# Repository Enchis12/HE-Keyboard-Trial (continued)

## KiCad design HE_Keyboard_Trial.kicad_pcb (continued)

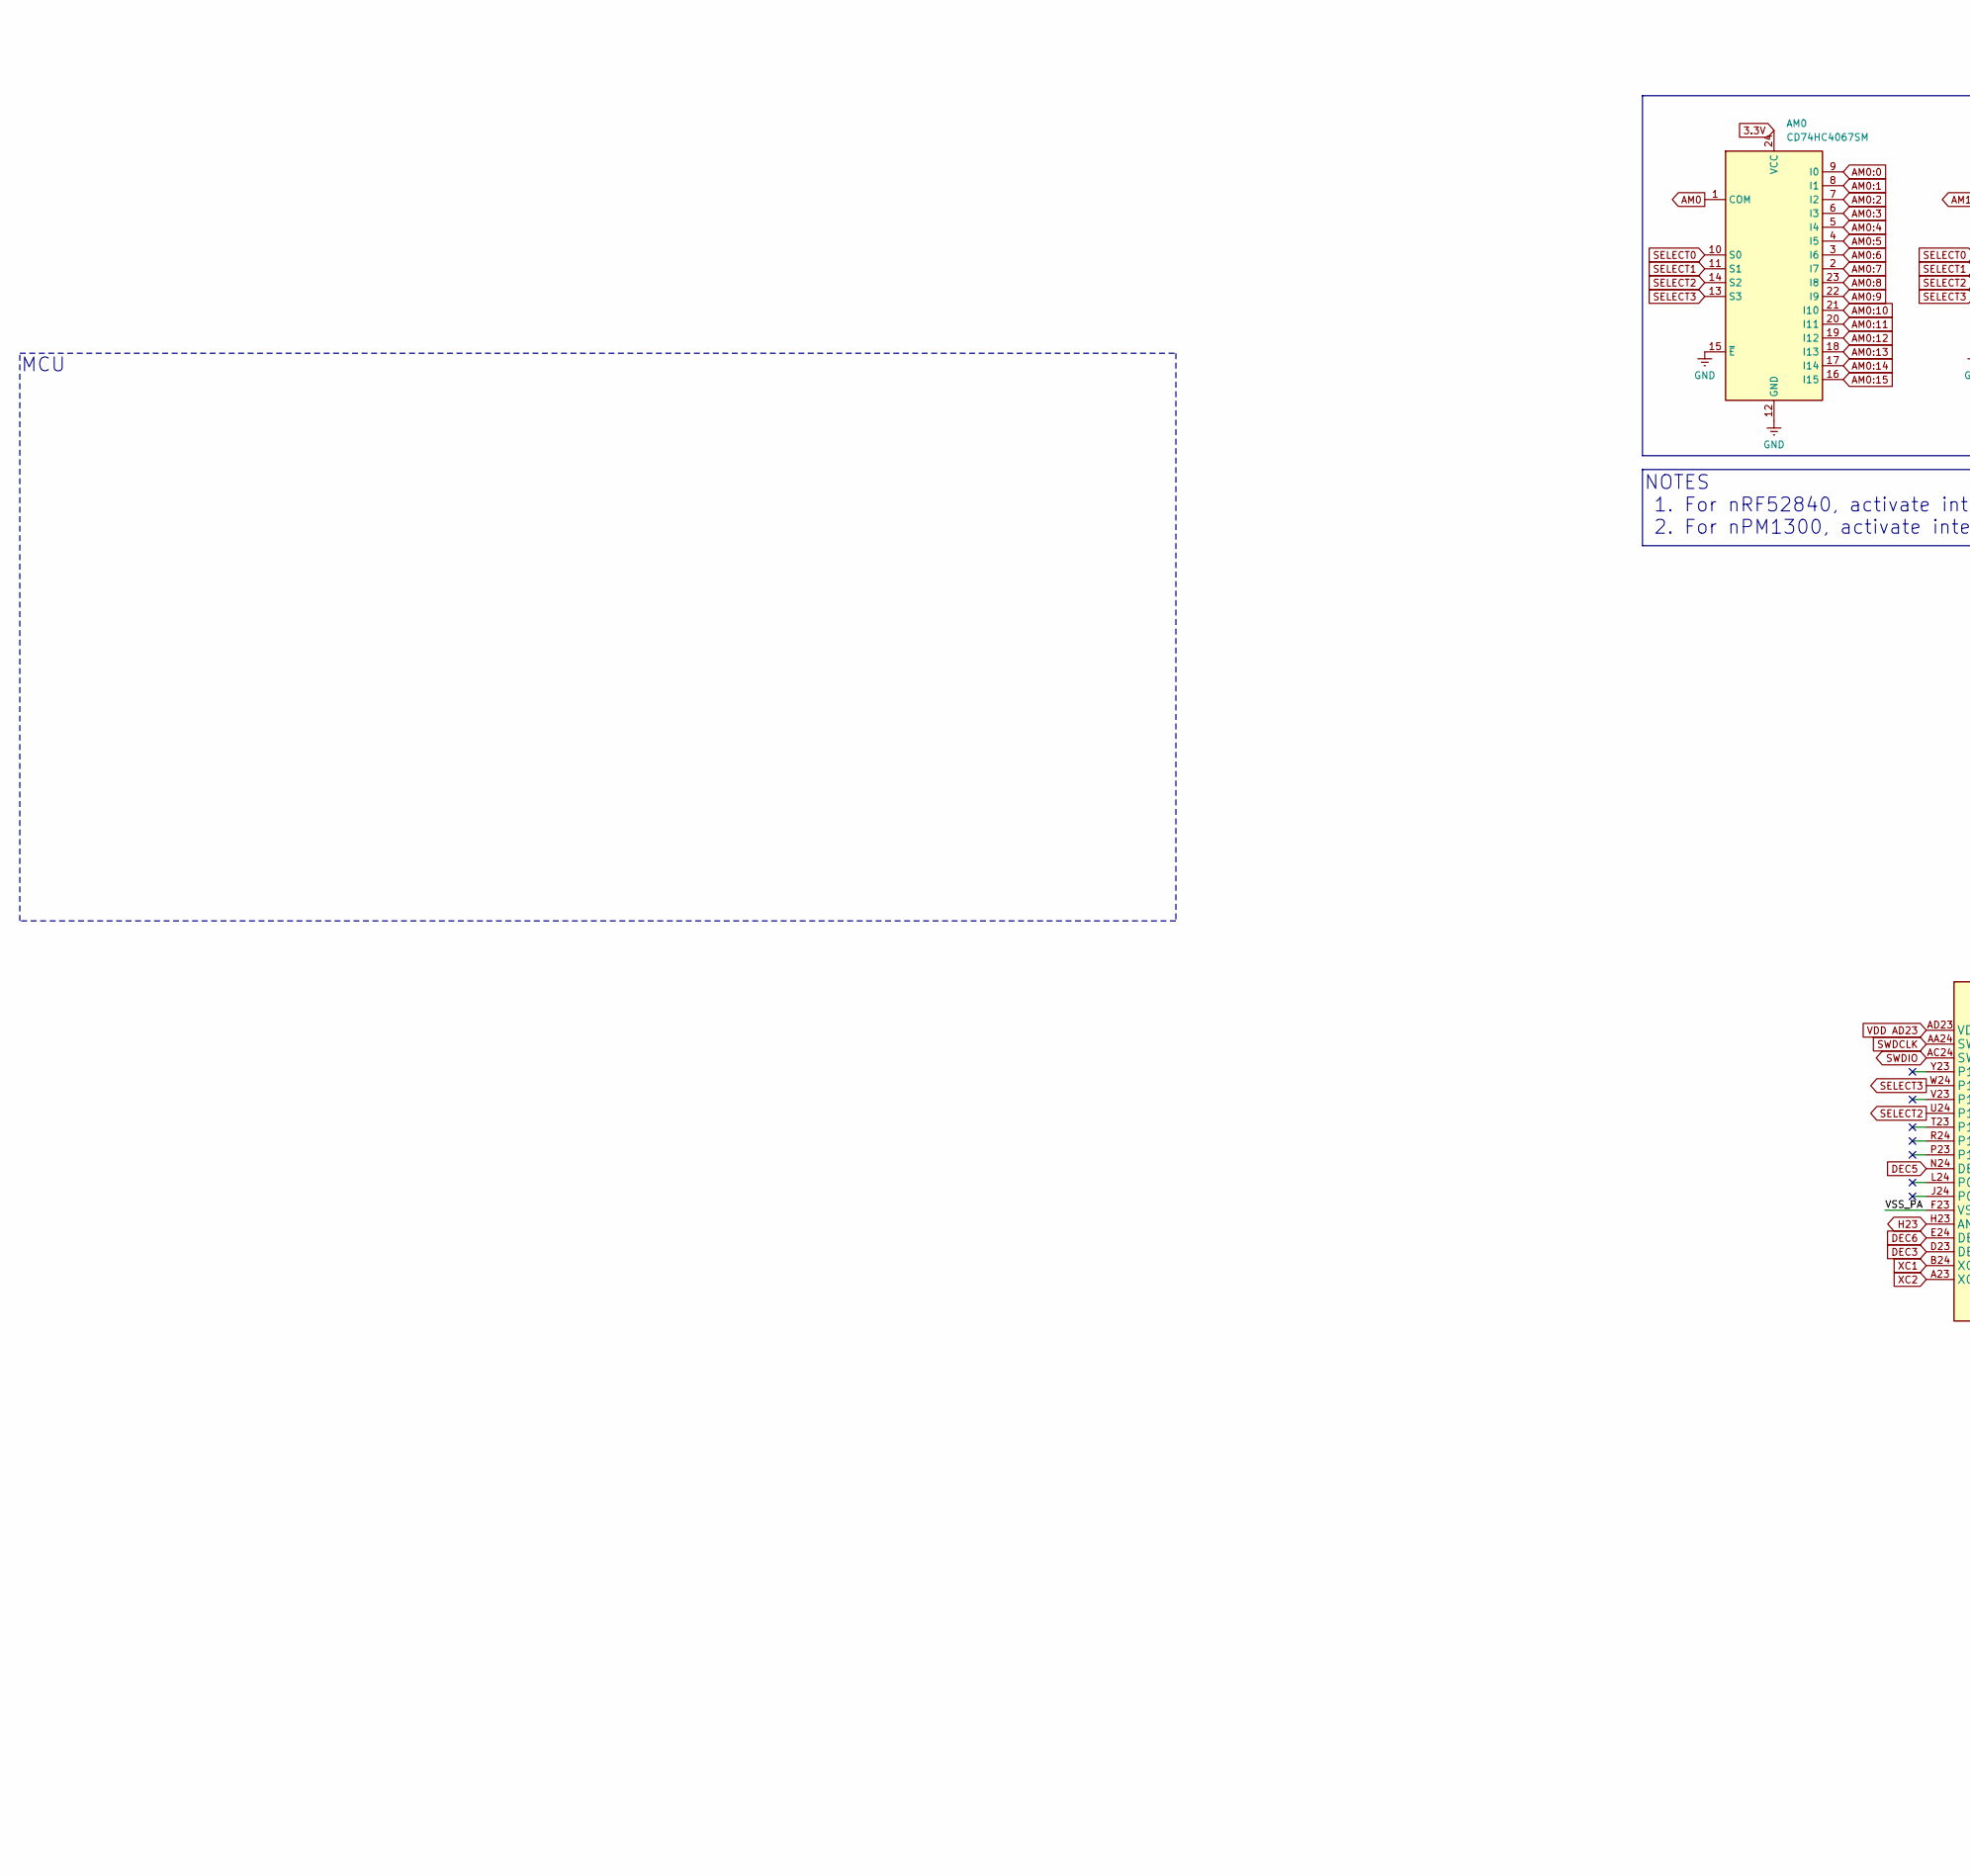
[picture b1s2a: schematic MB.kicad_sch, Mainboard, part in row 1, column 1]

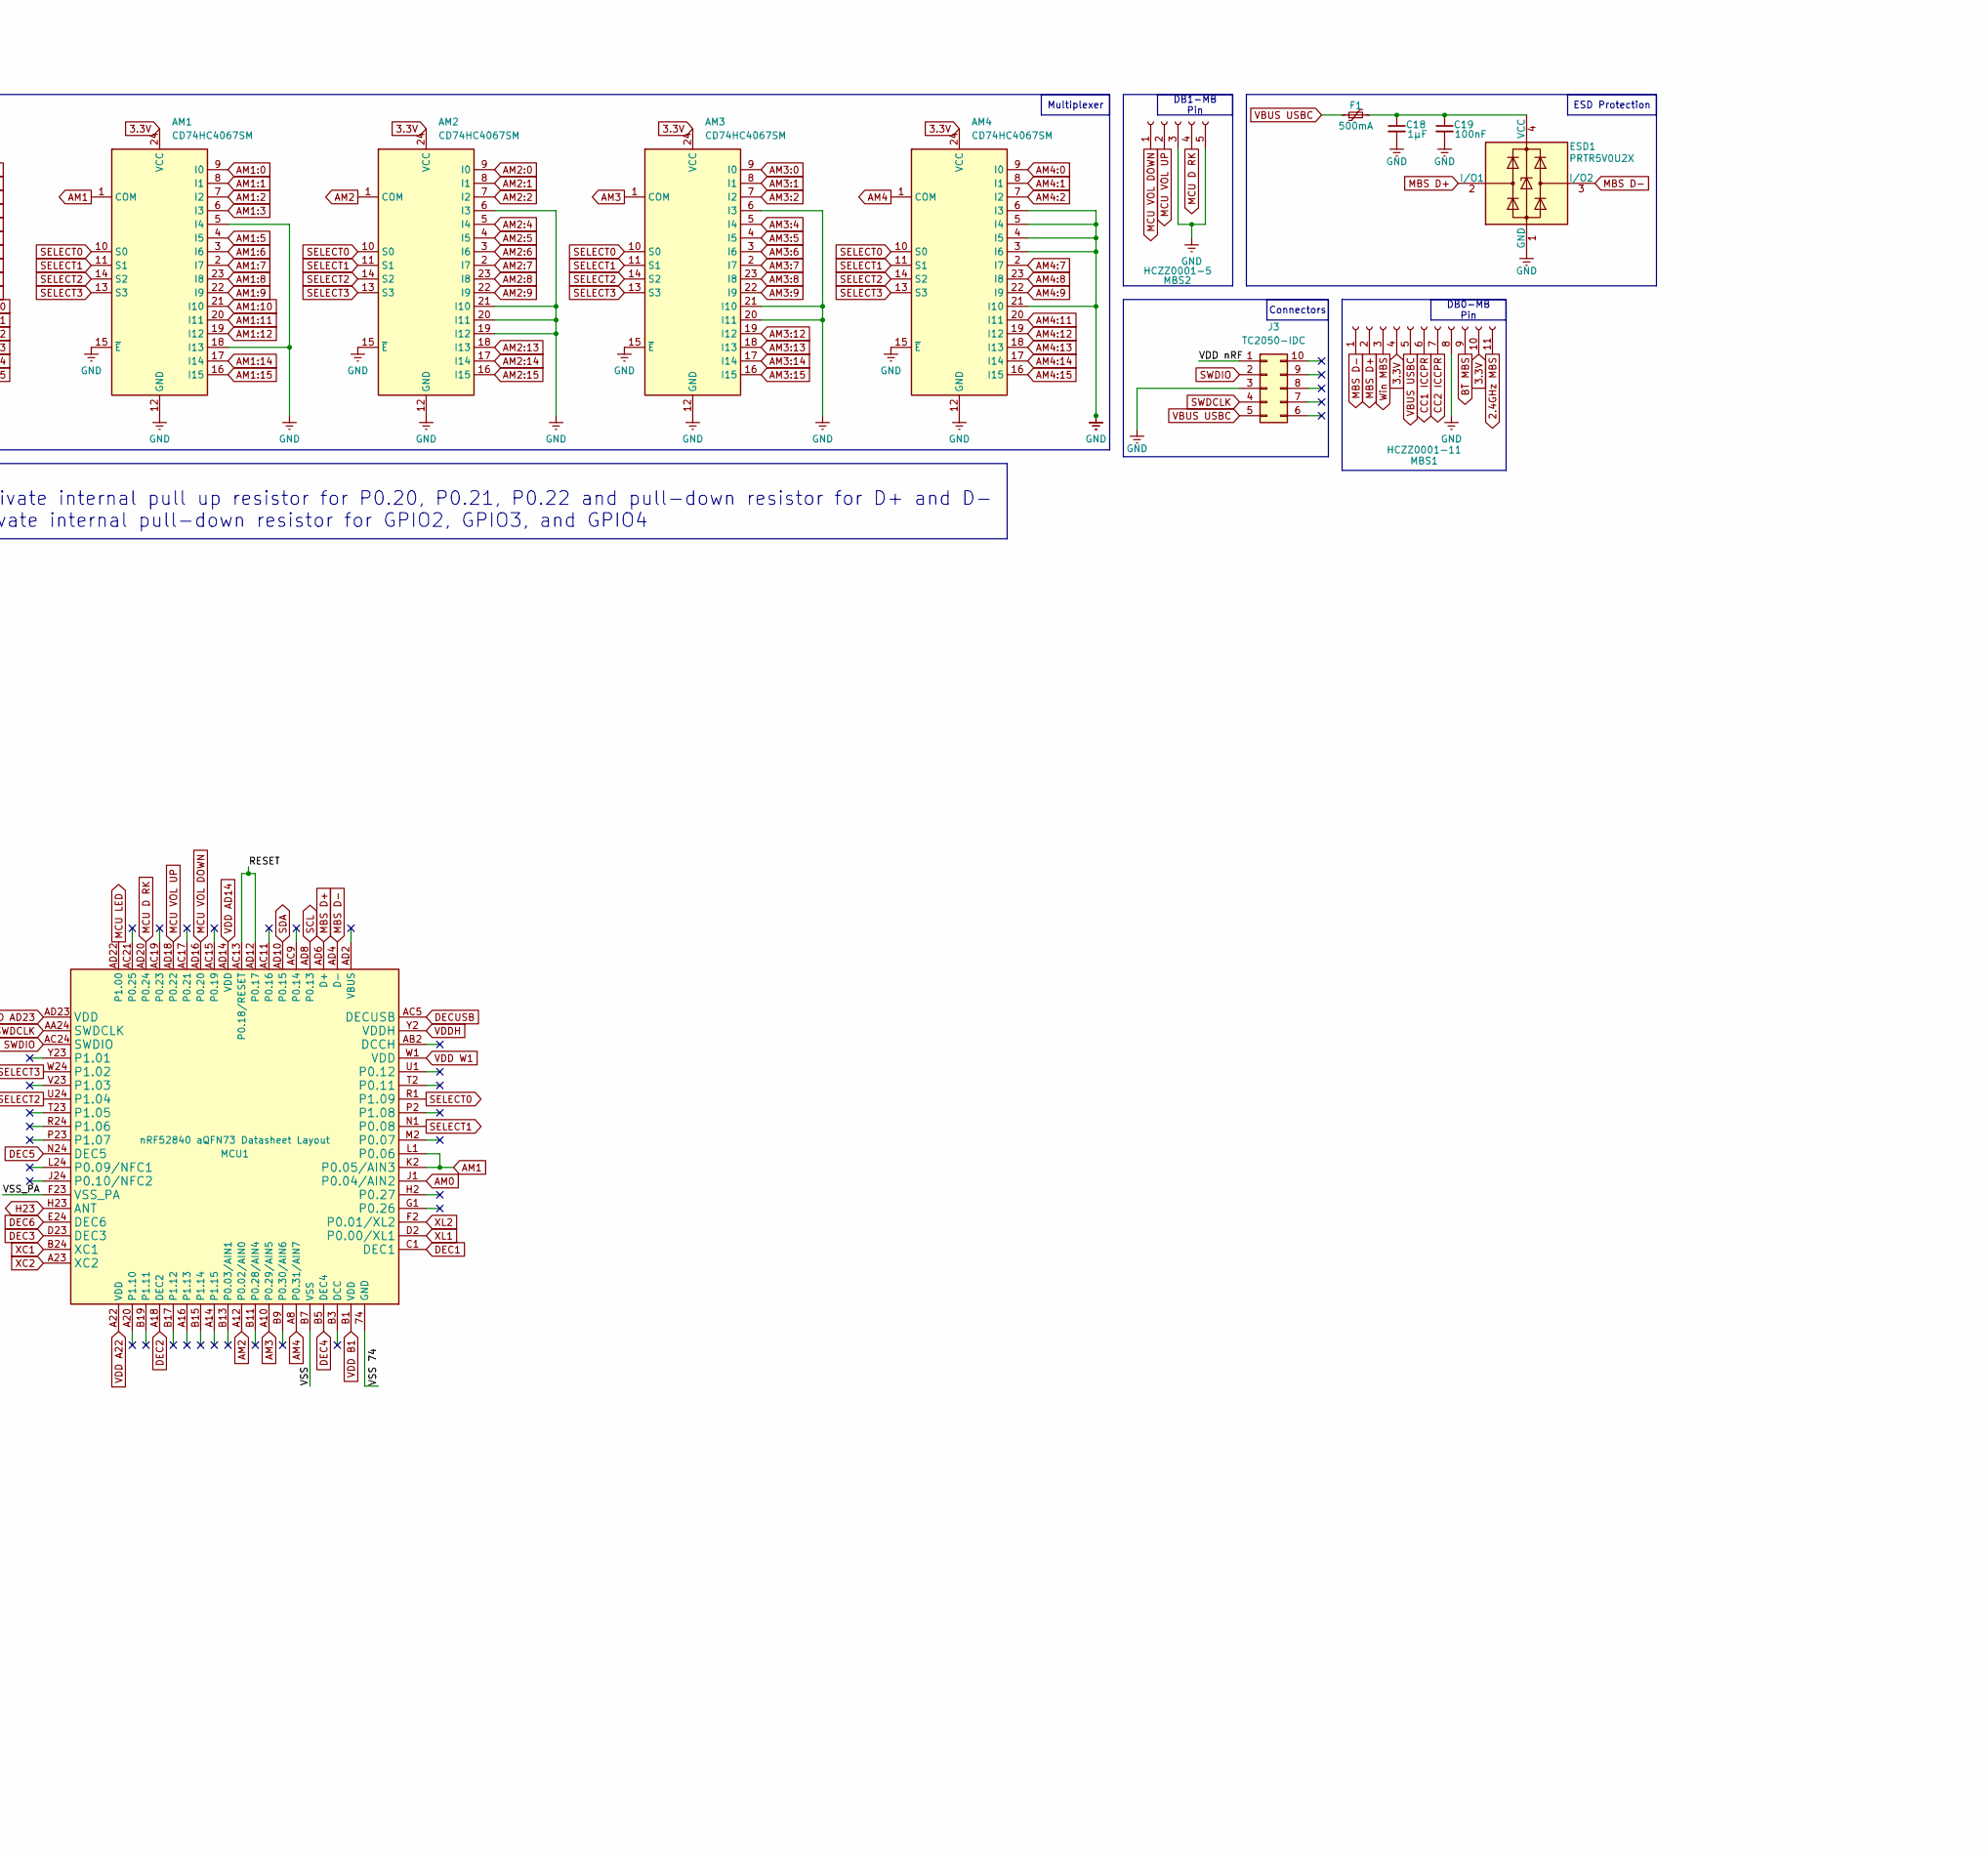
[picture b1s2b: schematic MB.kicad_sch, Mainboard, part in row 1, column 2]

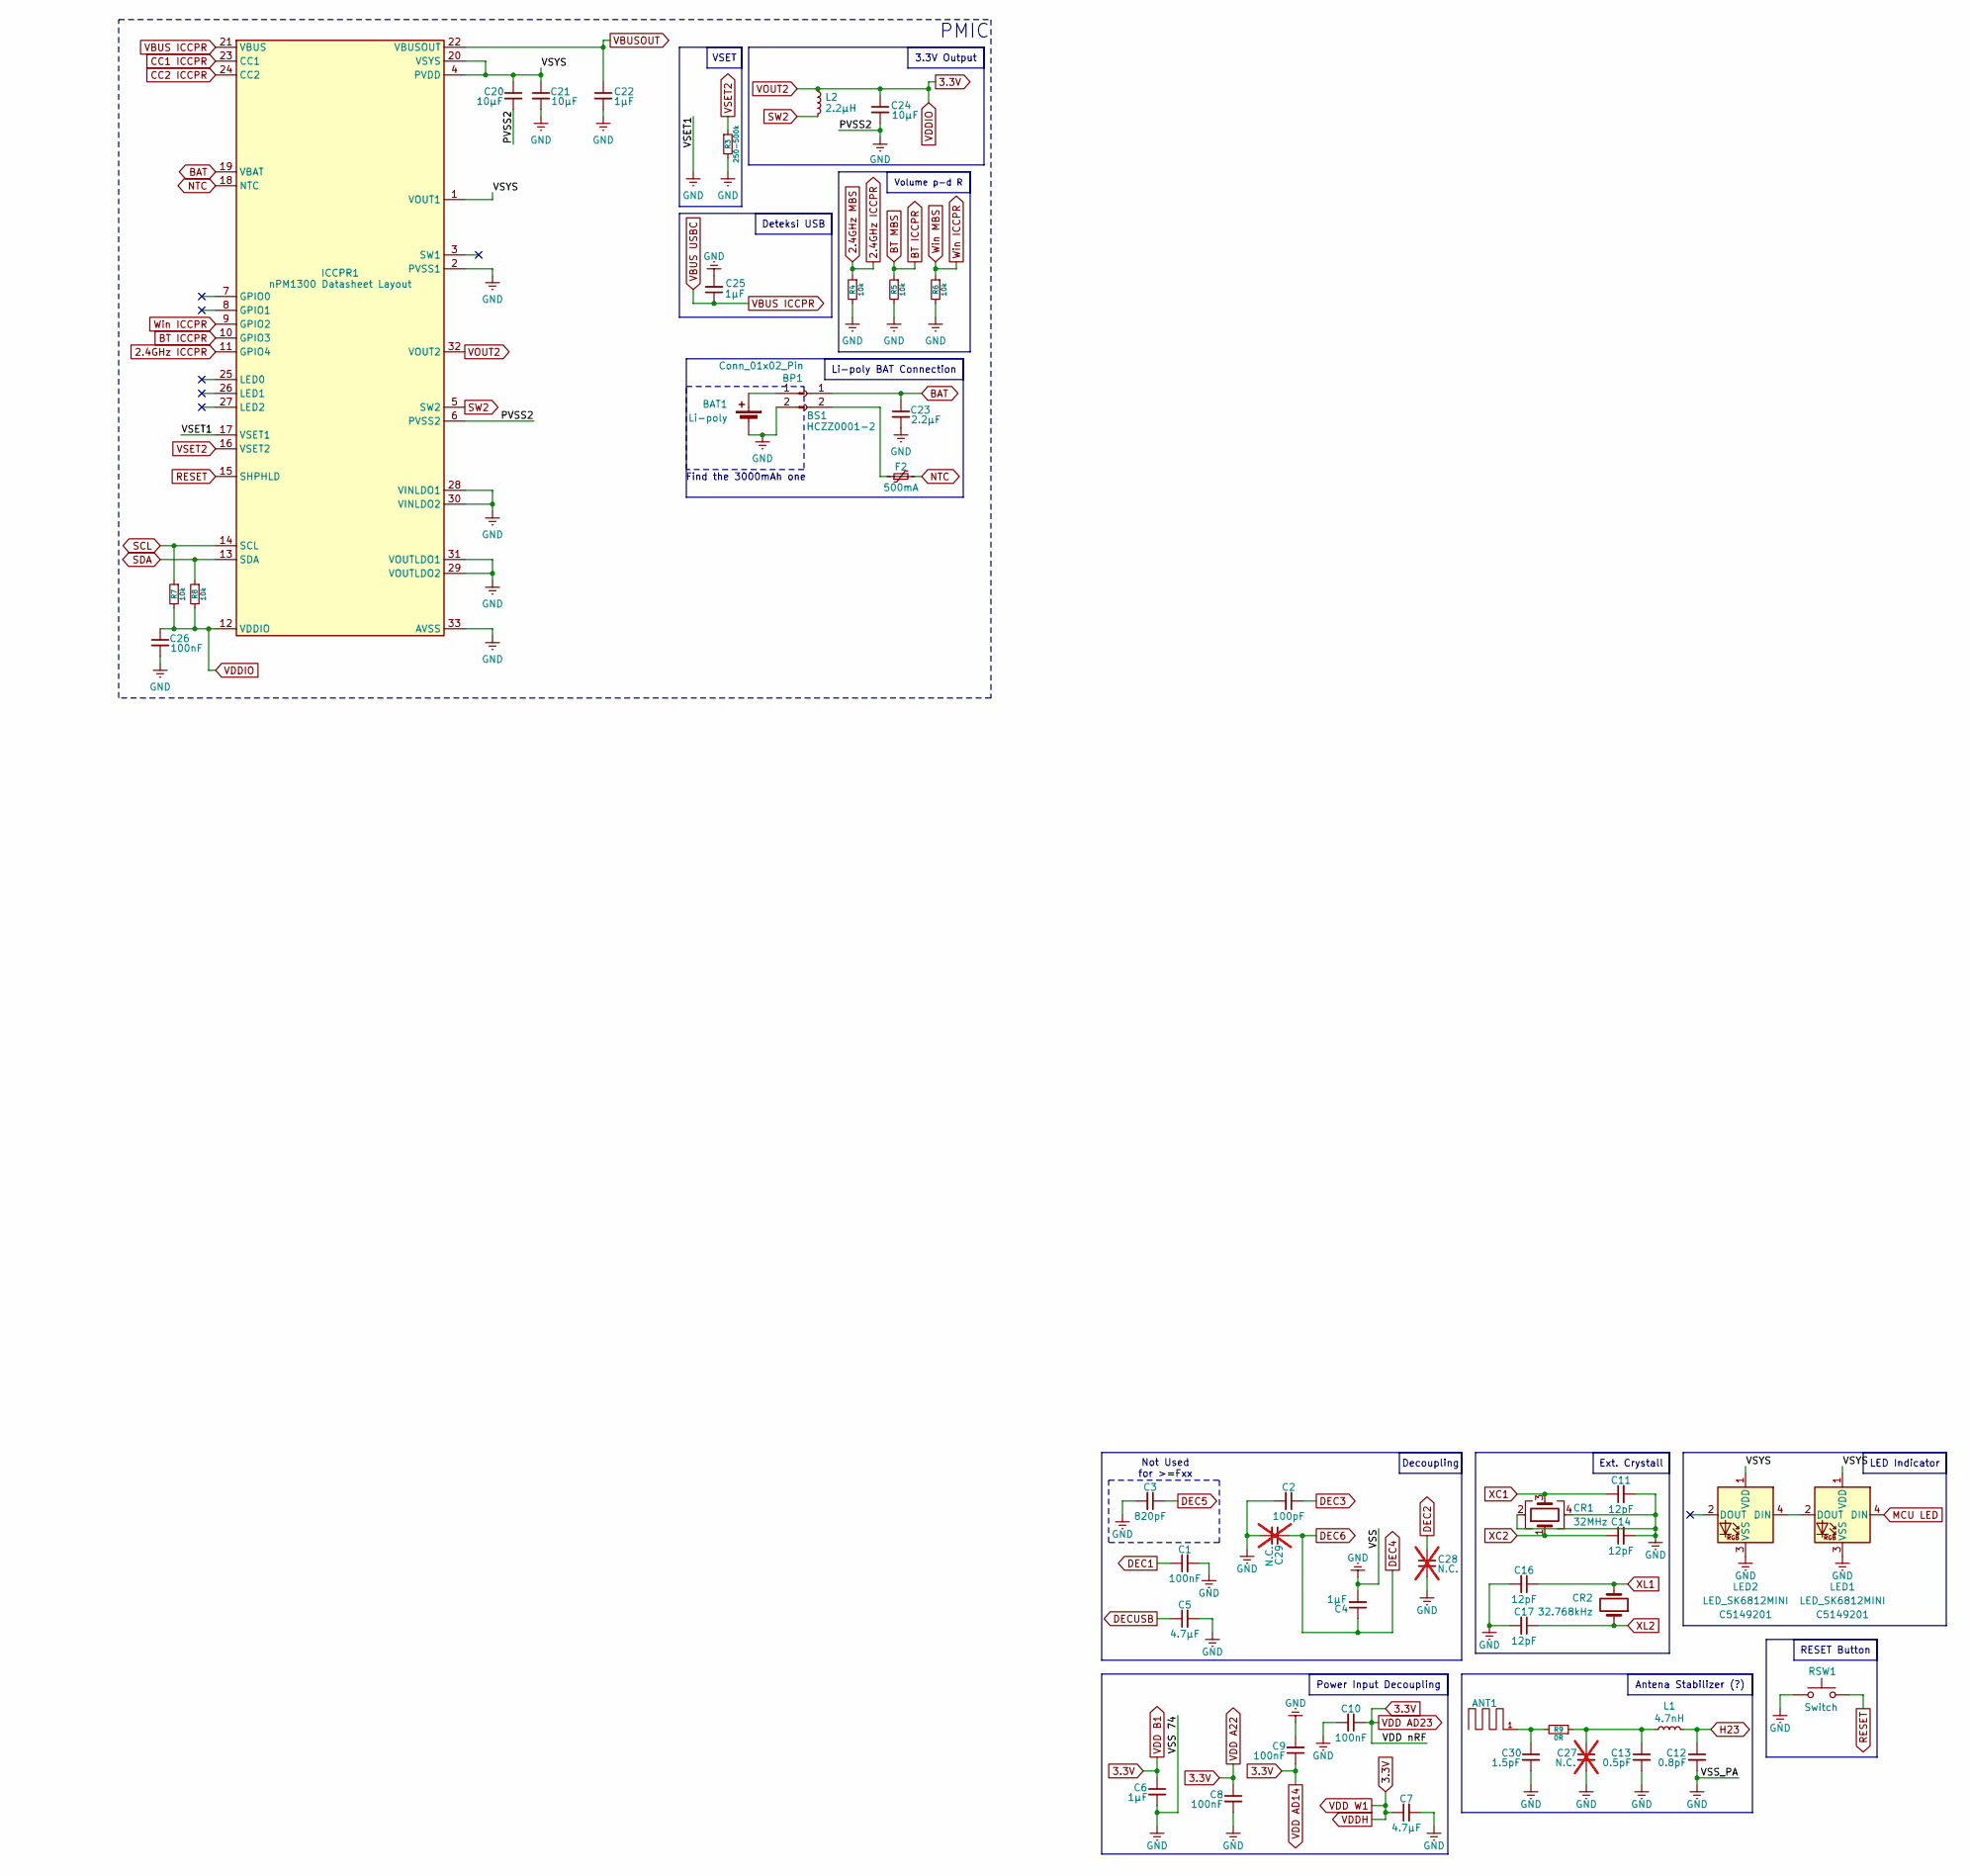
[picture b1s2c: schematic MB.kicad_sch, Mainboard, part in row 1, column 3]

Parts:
AM0, AM1, AM2, AM3, AM4: CD74HC4067SM; SSOP-24_5.3x8.2mm_P0.65mm; LCSC Part C98457
ANT1: MIFA
BAT1: Li-poly
BP1: Conn_01x02_Pin
BS1: HCZZ0001-2; Hong_Cheng_HCZZ0001-2; LCSC Part C7433453
C1, C8, C9, C10, C19: 100nF; Capacitor_0402
C2: 100pF; Capacitor_0402
C3: 820pF; Capacitor_0402
C4, C6, C22, C25: 1µF; Capacitor_0603
C5, C7: 4.7µF; Capacitor_0603
C11, C14, C16, C17: 12pF; Capacitor_0402
C12: 0.8pF; Capacitor_0402
C13: 0.5pF; Capacitor_0402
C18: 1µF; Capacitor_0402
C20, C21, C24: 10µF; Capacitor_0603
C23: 2.2µF; Capacitor_0603
C26: 100nF; C_0201_0603Metric
C27, C28, C29: N.C.; Capacitor_0402; not fitted
C30: 1.5pF; Capacitor_0402
CR1: 32MHz; Murata_Crystal_SMD_2016-4Pin_2.0x1.6mm; LCSC Part C914155
CR2: 32.768kHz; Crystal_SMD_3215-2Pin_3.2x1.5mm; LCSC Part C97605
ESD1: PRTR5V0U2X; SOT-143; LCSC Part C41409257
F1, F2: 500mA; Fuse_1206_3216Metric; LCSC Part C269112
ICCPR1: nPM1300 Datasheet Layout; Nordic_QFN-32-1EP_5x5mm_P0.5mm_EP3.6x3.6mm_ThermalVias; LCSC Part C7501206
J3: TC2050-IDC; Tag-Connect_TC2050-IDC-NL_2x05_P1.27mm_Vertical
L1: 4.7nH; L_0402_1005Metric; LCSC Part C3249625
L2: 2.2µH; Samsung_CIGT201610EH2R2MNE; LCSC Part C5185544
LED1, LED2: LED_SK6812MINI; LCSC C5149201
MBS1: HCZZ0001-11; Hong_Cheng_HCZZ0001-11; LCSC Part C7433462
MBS2: HCZZ0001-5; Hong_Cheng_HCZZ0001-5; LCSC Part C7433456
MCU1: nRF52840 aQFN73 Datasheet Layout; Nordic_AQFN-73-1EP_7x7mm_P0.5mm_Thermal
R3: 250-500k; R_0201_0603Metric
R4, R5, R6, R7, R8: 10k; R_0201_0603Metric
R9: 0R; R_0201_0603Metric
RSW1: Switch; Button_TL3342; LCSC Part C2886897

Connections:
2.4GHz ICCPR: ICCPR1.11 (GPIO4), MBS1.11, R4.1
3.3V: AM0.24 (VCC), AM1.24 (VCC), AM2.24 (VCC), AM3.24 (VCC), AM4.24 (VCC), C6.1, C7.1, C8.1, C9.1, C10.1, C24.1, C26.1, ICCPR1.12 (VDDIO), ICCPR1.32 (VOUT2), J3.1, L2.1, MBS1.4, MBS1.10, MCU1.A22 (VDD), MCU1.AD14 (VDD), MCU1.AD23 (VDD), MCU1.B1 (VDD), MCU1.W1 (VDD), MCU1.Y2 (VDDH), R7.2, R8.2; also elsewhere on the board
/Main Board/VSYS: C20.1, C21.1, ICCPR1.1 (VOUT1), ICCPR1.4 (PVDD), ICCPR1.20 (VSYS), LED1.1 (VDD), LED2.1 (VDD)
AM0: AM0.1 (COM), MCU1.J1 (P0.04/AIN2)
AM0:0: AM0.9 (I0); also elsewhere on the board
AM0:1: AM0.8 (I1); also elsewhere on the board
AM0:2: AM0.7 (I2); also elsewhere on the board
AM0:3: AM0.6 (I3); also elsewhere on the board
AM0:4: AM0.5 (I4); also elsewhere on the board
AM0:5: AM0.4 (I5); also elsewhere on the board
AM0:6: AM0.3 (I6); also elsewhere on the board
AM0:7: AM0.2 (I7); also elsewhere on the board
AM0:8: AM0.23 (I8); also elsewhere on the board
AM0:9: AM0.22 (I9); also elsewhere on the board
AM0:10: AM0.21 (I10); also elsewhere on the board
AM0:11: AM0.20 (I11); also elsewhere on the board
AM0:12: AM0.19 (I12); also elsewhere on the board
AM0:13: AM0.18 (I13); also elsewhere on the board
AM0:14: AM0.17 (I14); also elsewhere on the board
AM0:15: AM0.16 (I15); also elsewhere on the board
AM1: AM1.1 (COM), MCU1.K2 (P0.05/AIN3), MCU1.L1 (P0.06)
AM1:0: AM1.9 (I0); also elsewhere on the board
AM1:1: AM1.8 (I1); also elsewhere on the board
AM1:2: AM1.7 (I2); also elsewhere on the board
AM1:3: AM1.6 (I3); also elsewhere on the board
AM1:5: AM1.4 (I5); also elsewhere on the board
AM1:6: AM1.3 (I6); also elsewhere on the board
AM1:7: AM1.2 (I7); also elsewhere on the board
AM1:8: AM1.23 (I8); also elsewhere on the board
AM1:9: AM1.22 (I9); also elsewhere on the board
AM1:10: AM1.21 (I10); also elsewhere on the board
AM1:11: AM1.20 (I11); also elsewhere on the board
AM1:12: AM1.19 (I12); also elsewhere on the board
AM1:14: AM1.17 (I14); also elsewhere on the board
AM1:15: AM1.16 (I15); also elsewhere on the board
AM2: AM2.1 (COM), MCU1.A12 (P0.02/AIN0)
AM2:0: AM2.9 (I0); also elsewhere on the board
AM2:1: AM2.8 (I1); also elsewhere on the board
AM2:2: AM2.7 (I2); also elsewhere on the board
AM2:4: AM2.5 (I4); also elsewhere on the board
AM2:5: AM2.4 (I5); also elsewhere on the board
AM2:6: AM2.3 (I6); also elsewhere on the board
AM2:7: AM2.2 (I7); also elsewhere on the board
AM2:8: AM2.23 (I8); also elsewhere on the board
AM2:9: AM2.22 (I9); also elsewhere on the board
AM2:13: AM2.18 (I13); also elsewhere on the board
AM2:14: AM2.17 (I14); also elsewhere on the board
AM2:15: AM2.16 (I15); also elsewhere on the board
AM3: AM3.1 (COM), MCU1.A10 (P0.29/AIN5)
AM3:0: AM3.9 (I0); also elsewhere on the board
AM3:1: AM3.8 (I1); also elsewhere on the board
AM3:2: AM3.7 (I2); also elsewhere on the board
AM3:4: AM3.5 (I4); also elsewhere on the board
AM3:5: AM3.4 (I5); also elsewhere on the board
AM3:6: AM3.3 (I6); also elsewhere on the board
AM3:7: AM3.2 (I7); also elsewhere on the board
AM3:8: AM3.23 (I8); also elsewhere on the board
AM3:9: AM3.22 (I9); also elsewhere on the board
AM3:12: AM3.19 (I12); also elsewhere on the board
AM3:13: AM3.18 (I13); also elsewhere on the board
AM3:14: AM3.17 (I14); also elsewhere on the board
AM3:15: AM3.16 (I15); also elsewhere on the board
AM4: AM4.1 (COM), MCU1.A8 (P0.31/AIN7)
AM4:0: AM4.9 (I0); also elsewhere on the board
AM4:1: AM4.8 (I1); also elsewhere on the board
AM4:2: AM4.7 (I2); also elsewhere on the board
AM4:7: AM4.2 (I7); also elsewhere on the board
AM4:8: AM4.23 (I8); also elsewhere on the board
AM4:9: AM4.22 (I9); also elsewhere on the board
AM4:11: AM4.20 (I11); also elsewhere on the board
AM4:12: AM4.19 (I12); also elsewhere on the board
AM4:13: AM4.18 (I13); also elsewhere on the board
AM4:14: AM4.17 (I14); also elsewhere on the board
AM4:15: AM4.16 (I15); also elsewhere on the board
BAT: BS1.1, C23.1, ICCPR1.19 (VBAT)
BT ICCPR: ICCPR1.10 (GPIO3), MBS1.9, R5.1
CC1 ICCPR: ICCPR1.23 (CC1), MBS1.6
CC2 ICCPR: ICCPR1.24 (CC2), MBS1.7
DEC1: C1.1, MCU1.C1 (DEC1)
DEC2: C28.1, MCU1.A18 (DEC2)
DEC3: C2.1, MCU1.D23 (DEC3)
DEC4: C4.1, C29.1, MCU1.B5 (DEC4), MCU1.E24 (DEC6)
DEC5: C3.1, MCU1.N24 (DEC5)
DECUSB: C5.1, MCU1.AC5 (DECUSB)
GND: AM0.12 (GND), AM0.15 (~E), AM1.5 (I4), AM1.12 (GND), AM1.15 (~E), AM1.18 (I13), AM2.6 (I3), AM2.12 (GND), AM2.15 (~E), AM2.19 (I12), AM2.20 (I11), AM2.21 (I10), AM3.6 (I3), AM3.12 (GND), AM3.15 (~E), AM3.20 (I11), AM3.21 (I10), AM4.3 (I6), AM4.4 (I5), AM4.5 (I4), AM4.6 (I3), AM4.12 (GND), AM4.15 (~E), AM4.21 (I10), BAT1.2 (-), BP1.2, C1.2, C2.2, C3.2, C4.2, C5.2, C6.2, C7.2, C8.2, C9.2, C10.2, C11.2, C12.2, C13.2, C14.2, C16.2, C17.2, C18.2, C19.2, C20.2, C21.2, C22.2, C23.2, C24.2, C25.2, C26.2, C27.2, C28.2, C29.2, C30.2, CR1.2, CR1.4, ESD1.1 (GND), ICCPR1.2 (PVSS1), ICCPR1.6 (PVSS2), ICCPR1.17 (VSET1), ICCPR1.28 (VINLDO1), ICCPR1.29 (VOUTLDO2), ICCPR1.30 (VINLDO2), ICCPR1.31 (VOUTLDO1), ICCPR1.33 (AVSS), J3.3, LED1.3 (VSS), LED2.3 (VSS), MBS1.8, MBS2.3, MBS2.5, MCU1.74 (GND), MCU1.B7 (VSS), MCU1.F23 (VSS_PA), R3.2, R4.2, R5.2, R6.2, RSW1.1; also elsewhere on the board
H23: C12.1, L1.1, MCU1.H23 (ANT)
MBS D+: ESD1.2 (I/O1), MBS1.2, MCU1.AD6 (D+)
MBS D-: ESD1.3 (I/O2), MBS1.1, MCU1.AD4 (D-)
MCU D RK: MBS2.4, MCU1.AD20 (P0.24)
MCU LED: LED1.4 (DIN), MCU1.AD22 (P1.00)
MCU VOL DOWN: MBS2.1, MCU1.AD16 (P0.20)
MCU VOL UP: MBS2.2, MCU1.AD18 (P0.22)
NTC: F2.2, ICCPR1.18 (NTC)
unnamed: ANT1.1, C30.1, R9.2
unnamed: BAT1.1 (+), BP1.1
unnamed: BS1.2, F2.1
unnamed: C13.1, C27.1, L1.2, R9.1
unnamed: C18.1, C19.1, ESD1.4 (VCC), F1.2
unnamed: LED1.2 (DOUT), LED2.4 (DIN)
RESET: ICCPR1.15 (SHPHLD), MCU1.AC13 (P0.18/RESET), MCU1.AD12 (P0.17), RSW1.2
SCL: ICCPR1.14 (SCL), MCU1.AD8 (P0.13), R7.1
SDA: ICCPR1.13 (SDA), MCU1.AD10 (P0.15), R8.1
SELECT0: AM0.10 (S0), AM1.10 (S0), AM2.10 (S0), AM3.10 (S0), AM4.10 (S0), MCU1.R1 (P1.09)
SELECT1: AM0.11 (S1), AM1.11 (S1), AM2.11 (S1), AM3.11 (S1), AM4.11 (S1), MCU1.N1 (P0.08)
SELECT2: AM0.14 (S2), AM1.14 (S2), AM2.14 (S2), AM3.14 (S2), AM4.14 (S2), MCU1.U24 (P1.04)
SELECT3: AM0.13 (S3), AM1.13 (S3), AM2.13 (S3), AM3.13 (S3), AM4.13 (S3), MCU1.W24 (P1.02)
SW2: ICCPR1.5 (SW2), L2.2
SWDCLK: J3.4, MCU1.AA24 (SWDCLK)
SWDIO: J3.2, MCU1.AC24 (SWDIO)
VBUS ICCPR: C25.1, F1.1, ICCPR1.21 (VBUS), J3.5, MBS1.5; also elsewhere on the board
VBUSOUT: C22.1, ICCPR1.22 (VBUSOUT)
VSET2: ICCPR1.16 (VSET2), R3.1
Win ICCPR: ICCPR1.9 (GPIO2), MBS1.3, R6.1
XC1: C11.1, CR1.3, MCU1.B24 (XC1)
XC2: C14.1, CR1.1, MCU1.A23 (XC2)
XL1: C16.1, CR2.2, MCU1.D2 (P0.00/XL1)
XL2: C17.1, CR2.1, MCU1.F2 (P0.01/XL2)

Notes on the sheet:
Antena Stabilizer (?)
Volume p-d R
LED Indicator
DB1-MB Pin
1. For nRF52840, activate internal pull up resistor for P0.20, P0.21, P0.22 and pull-down resistor for D+ and D- 2. For nPM1300, activate internal pull-down resistor for GPIO2, GPIO3, and GPIO4
Connectors
Multiplexer
RESET Button
3.3V Output
Ext. Crystall
Li-poly BAT Connection
Decoupling
Power Input Decoupling
ESD Protection
Deteksi USB
DB0-MB Pin
VSET
MCU
Find the 3000mAh one
PMIC
Not Used for >=Fxx
NOTES

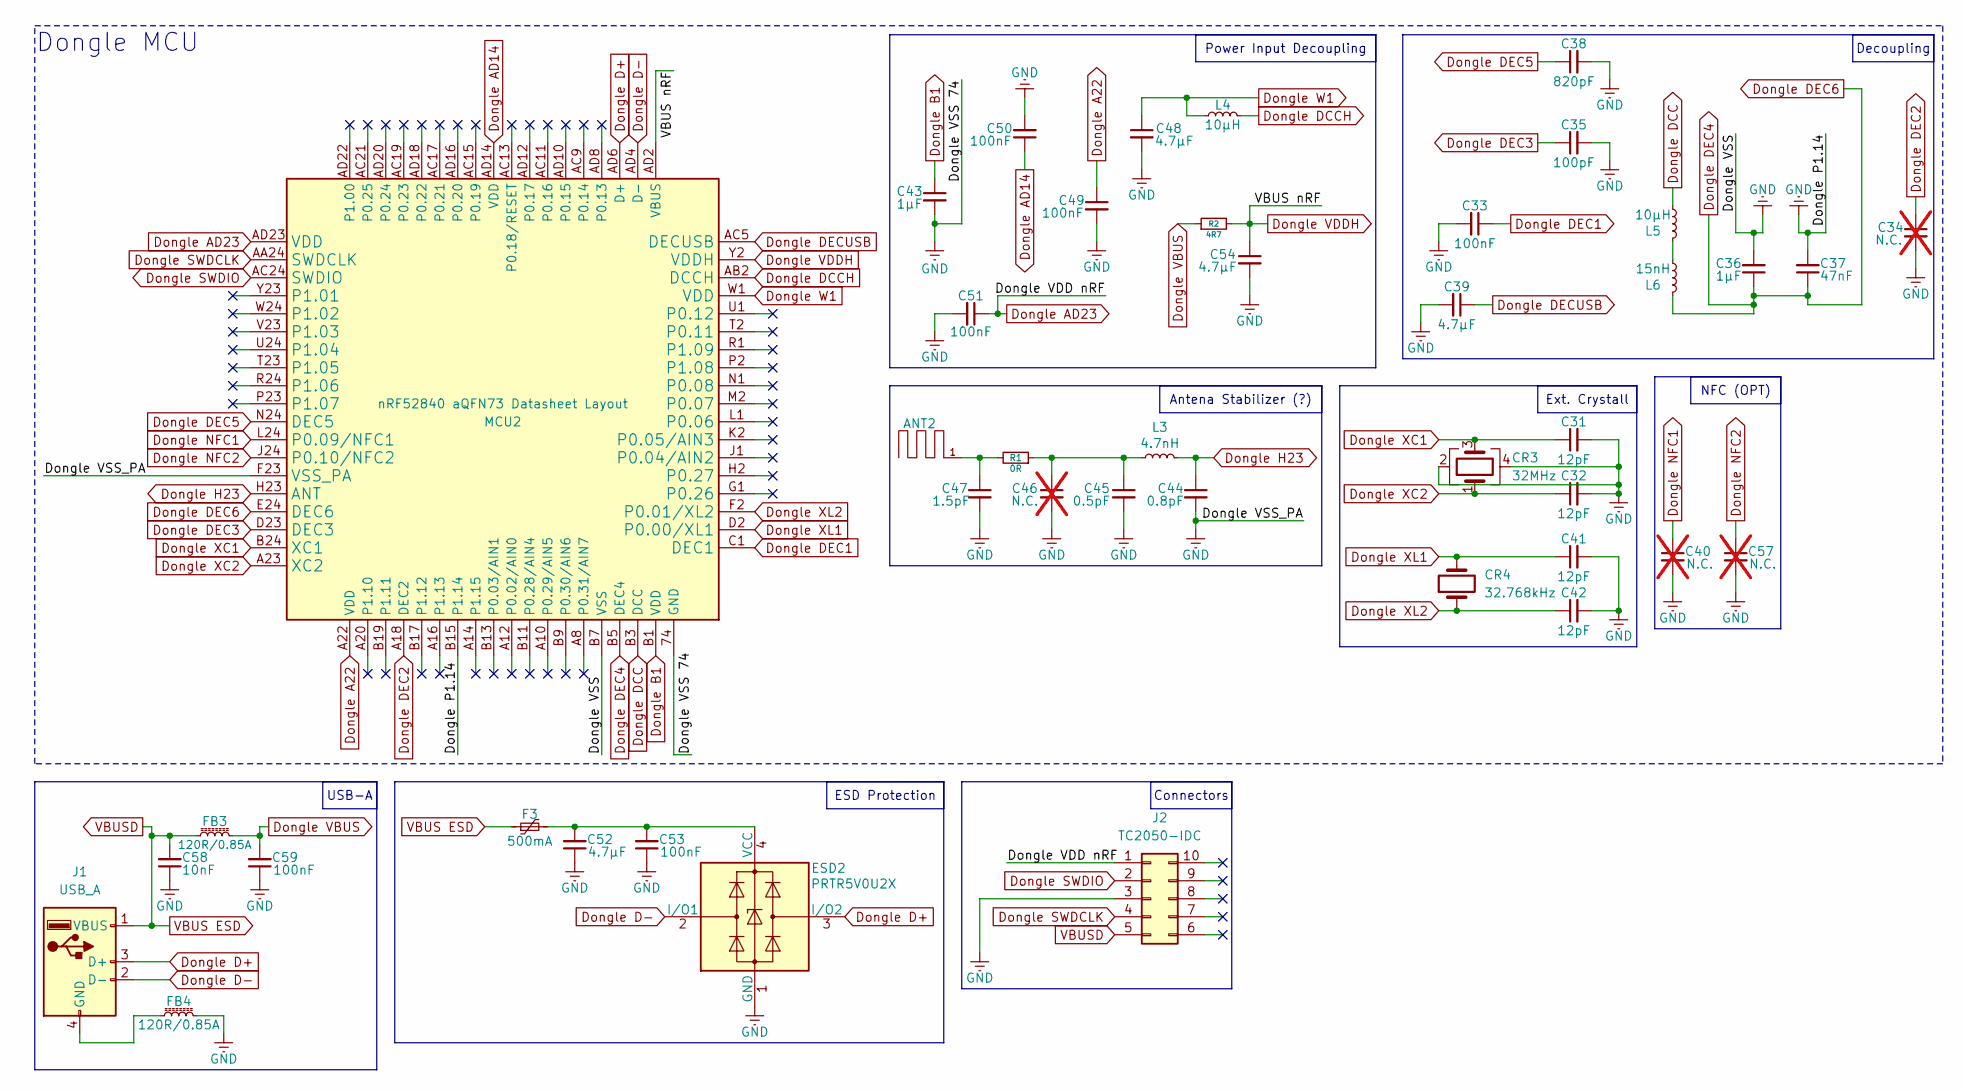
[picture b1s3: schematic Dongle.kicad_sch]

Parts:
ANT2: MIFA
C31, C32, C41, C42: 12pF; C_0201_0603Metric
C33, C49, C50, C51, C53, C59: 100nF; C_0201_0603Metric
C34, C40, C46, C57: N.C.; C_0201_0603Metric; not fitted
C35: 100pF; C_0201_0603Metric; LCSC Part C710791
C36, C43: 1µF; Capacitor_0603
C37: 47nF; C_0201_0603Metric
C38: 820pF; C_0201_0603Metric
C39, C48: 4.7µF; Capacitor_0603
C44: 0.8pF; C_0201_0603Metric
C45: 0.5pF; C_0201_0603Metric; LCSC Part C2981049
C47: 1.5pF; C_0201_0603Metric
C52, C54: 4.7µF; Capacitor_0402
C58: 10nF; C_0201_0603Metric
CR3: 32MHz; Murata_Crystal_SMD_2016-4Pin_2.0x1.6mm; LCSC Part C914155
CR4: 32.768kHz; Crystal_SMD_2012-2Pin_2.0x1.2mm; LCSC Part C97603
ESD2: PRTR5V0U2X; SOT-143; LCSC Part C41409257
F3: 500mA; Fuse_1206_3216Metric; LCSC Part C269112
FB3, FB4: 120R/0.85A; L_0201_0603Metric; LCSC Part C2661865
J1: USB_A; USB A
J2: TC2050-IDC; Tag-Connect_TC2050-IDC-NL_2x05_P1.27mm_Vertical
L3: 4.7nH; L_0201_0603Metric; LCSC Part C86126
L4, L5: 10µH; L_0603_1608Metric; LCSC Part C87216
L6: 15nH; L_0402_1005Metric; LCSC Part C87189
MCU2: nRF52840 aQFN73 Datasheet Layout; Nordic_AQFN-73-1EP_7x7mm_P0.5mm_Thermal
R1: 0R; R_0201_0603Metric
R2: 4R7; R_0201_0603Metric

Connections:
Dongle A22: C49.1, MCU2.A22 (VDD)
Dongle AD14: C50.1, MCU2.AD14 (VDD)
Dongle AD23: C51.1, J2.1, MCU2.AD23 (VDD)
Dongle B1: C43.1, MCU2.B1 (VDD)
Dongle D+: ESD2.3 (I/O2), J1.3 (D+), MCU2.AD6 (D+)
Dongle D-: ESD2.2 (I/O1), J1.2 (D-), MCU2.AD4 (D-)
Dongle DCC: L5.1, MCU2.B3 (DCC)
Dongle DCCH: L4.2, MCU2.AB2 (DCCH)
Dongle DEC1: C33.1, MCU2.C1 (DEC1)
Dongle DEC2: C34.1, MCU2.A18 (DEC2)
Dongle DEC3: C35.1, MCU2.D23 (DEC3)
Dongle DEC4: C36.1, C37.1, L6.2, MCU2.B5 (DEC4), MCU2.E24 (DEC6)
Dongle DEC5: C38.1, MCU2.N24 (DEC5)
Dongle DECUSB: C39.1, MCU2.AC5 (DECUSB)
Dongle H23: C44.1, L3.1, MCU2.H23 (ANT)
Dongle NFC1: C40.1, MCU2.L24 (P0.09/NFC1)
Dongle NFC2: C57.1, MCU2.J24 (P0.10/NFC2)
Dongle SWDCLK: J2.4, MCU2.AA24 (SWDCLK)
Dongle SWDIO: J2.2, MCU2.AC24 (SWDIO)
Dongle VBUS: C59.2, FB3.2, R2.1
Dongle VDDH: C54.1, MCU2.AD2 (VBUS), MCU2.Y2 (VDDH), R2.2
Dongle W1: C48.1, L4.1, MCU2.W1 (VDD)
Dongle XC1: C31.1, CR3.3, MCU2.B24 (XC1)
Dongle XC2: C32.1, CR3.1, MCU2.A23 (XC2)
Dongle XL1: C41.1, CR4.2, MCU2.D2 (P0.00/XL1)
Dongle XL2: C42.1, CR4.1, MCU2.F2 (P0.01/XL2)
GND: C31.2, C32.2, C33.2, C34.2, C35.2, C36.2, C37.2, C38.2, C39.2, C40.2, C41.2, C42.2, C43.2, C44.2, C45.2, C46.2, C47.2, C48.2, C49.2, C50.2, C51.2, C52.1, C53.1, C54.2, C57.2, C58.1, C59.1, CR3.2, CR3.4, ESD2.1 (GND), FB4.2, J2.3, MCU2.74 (GND), MCU2.B7 (VSS), MCU2.B15 (P1.14), MCU2.F23 (VSS_PA); also elsewhere on the board
unnamed: ANT2.1, C47.1, R1.2
unnamed: C45.1, C46.1, L3.2, R1.1
unnamed: C52.2, C53.2, ESD2.4 (VCC), F3.2
unnamed: FB4.1, J1.4 (GND)
unnamed: L5.2, L6.1
VBUS ESD: C58.2, F3.1, FB3.1, J1.1 (VBUS), J2.5

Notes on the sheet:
USB-A
Decoupling
NFC (OPT)
Antena Stabilizer (?)
Ext. Crystall
Power Input Decoupling
ESD Protection
Connectors
Dongle MCU

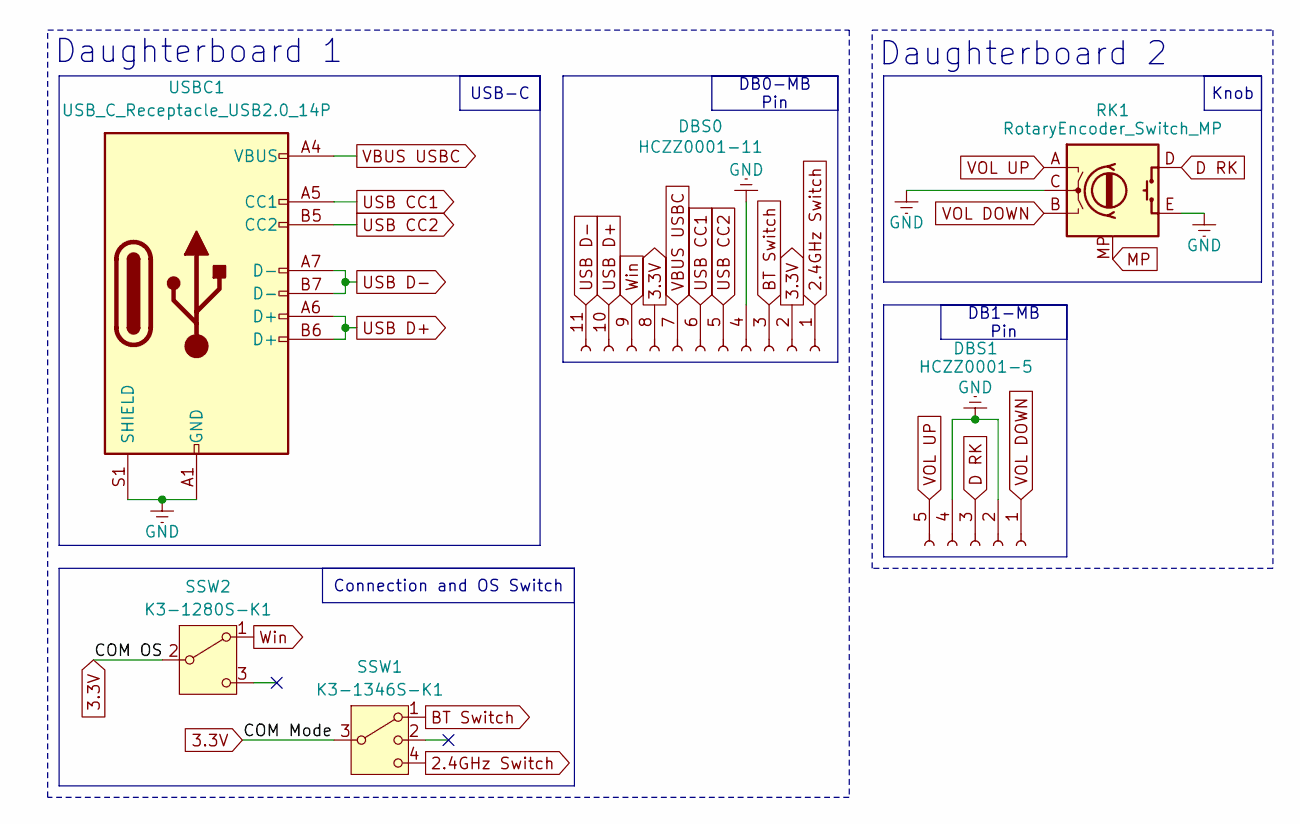
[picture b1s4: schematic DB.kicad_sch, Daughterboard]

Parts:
DBS0: HCZZ0001-11; Hong_Cheng_HCZZ0001-11; LCSC Part C7433462
DBS1: HCZZ0001-5; Hong_Cheng_HCZZ0001-5; LCSC Part C7433456
RK1: RotaryEncoder_Switch_MP; RotaryEncoder_CTR_ED11601M-FB15A7.0-C15-202; LCSC Part C470592
SSW1: K3-1346S-K1; SW_SP3T_Korean_Hroparts_Elec_K3-1346S-K1; LCSC Part C128957
SSW2: K3-1280S-K1; SW_SPDT_Korean_Hroparts_Elec_K3-1280S-K1; LCSC Part C128953
USBC1: USB_C_Receptacle_USB2.0_14P; USB_C_HRO_TYPE-C-31-M-12; LCSC Part C165948

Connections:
2.4GHz Switch: DBS0.1, SSW1.4
3.3V: DBS0.2, DBS0.8, SSW1.3, SSW2.2 (B); also elsewhere on the board
BT Switch: DBS0.3, SSW1.1
D RK: DBS1.3, RK1.D
GND: DBS0.4, DBS1.2, DBS1.4, RK1.C, RK1.E (S2), USBC1.A1 (GND), USBC1.A12 (GND), USBC1.B1 (GND), USBC1.B12 (GND), USBC1.S1 (SHIELD); also elsewhere on the board
MP: RK1.MP
USB CC1: DBS0.6, USBC1.A5 (CC1)
USB CC2: DBS0.5, USBC1.B5 (CC2)
USB D+: DBS0.10, USBC1.A6 (D+), USBC1.B6 (D+)
USB D-: DBS0.11, USBC1.A7 (D-), USBC1.B7 (D-)
VBUS ICCPR: DBS0.7, USBC1.A4 (VBUS), USBC1.A9 (VBUS), USBC1.B4 (VBUS), USBC1.B9 (VBUS); also elsewhere on the board
VOL DOWN: DBS1.1, RK1.B
VOL UP: DBS1.5, RK1.A
Win: DBS0.9, SSW2.1 (A)

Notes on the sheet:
Knob
Connection and OS Switch
DB1-MB Pin
DB0-MB Pin
USB-C
Daughterboard 2
Daughterboard 1
